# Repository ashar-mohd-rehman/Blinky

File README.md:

Blinky Board is 555 blinky pcb where 10leds blink. The speed can be adjusted via on board potentiometer. Since ne555
timer doesnt have enough pins we use cd4017 gpio extender for using 10 leds

# Schematic #

# Pcb #

# 3d model # 

# Render #

link to BOM : https://docs.google.com/spreadsheets/d/1oSV3quS0oqQWDv8-AmcpKySihurtdW80pACxGFzfaJI/edit?usp=sharing

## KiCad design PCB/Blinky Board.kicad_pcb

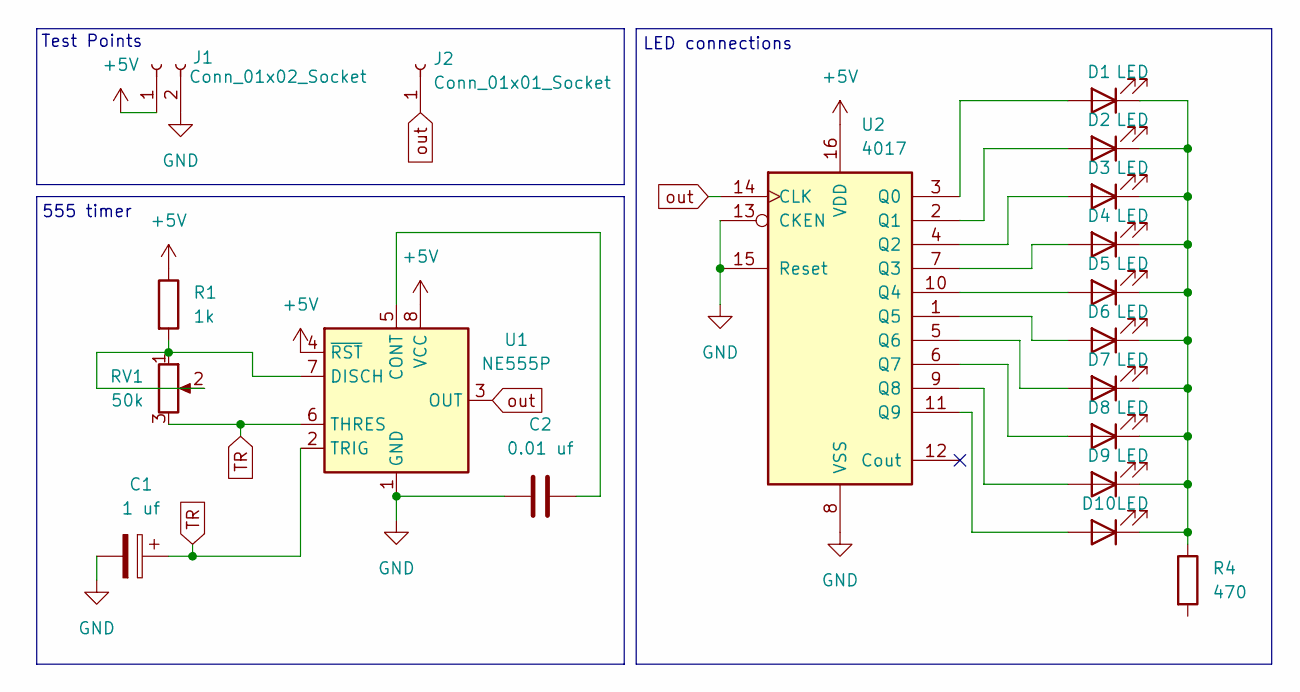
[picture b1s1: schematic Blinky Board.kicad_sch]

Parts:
C1: 1 uf; CP_Radial_D5.0mm_P2.00mm
C2: 0.01 uf; C_Disc_D7.5mm_W2.5mm_P5.00mm
D1, D2, D3, D4, D5, D6, D7, D8, D9, D10: LED; LED_D3.0mm
J1: Conn_01x02_Socket; PinHeader_1x02_P2.54mm_Vertical
J2: Conn_01x01_Socket; PinHeader_1x01_P2.54mm_Vertical
R1: 1k; R_Axial_DIN0207_L6.3mm_D2.5mm_P7.62mm_Horizontal
R4: 470; R_Axial_DIN0207_L6.3mm_D2.5mm_P7.62mm_Horizontal
RV1: 50k; Potentiometer_Vishay_T93YA_Vertical
U1: NE555P; DIP-8_W7.62mm
U2: 4017; CD4017

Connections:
+5V: J1.1, R1.1, U1.4 (~RST), U1.8 (VCC), U2.16 (VDD)
GND: C1.2, C2.1, J1.2, U1.1 (GND), U2.8 (VSS), U2.13 (CKEN), U2.15 (Reset)
unnamed: D1.2 (A), U2.3 (Q0)
unnamed: D1.1 (K), D2.1 (K), D3.1 (K), D4.1 (K), D5.1 (K), D6.1 (K), D7.1 (K), D8.1 (K), D9.1 (K), D10.1 (K), R4.1
unnamed: D2.2 (A), U2.2 (Q1)
unnamed: D3.2 (A), U2.4 (Q2)
unnamed: D4.2 (A), U2.7 (Q3)
unnamed: D5.2 (A), U2.10 (Q4)
unnamed: D6.2 (A), U2.1 (Q5)
unnamed: D7.2 (A), U2.5 (Q6)
unnamed: D8.2 (A), U2.6 (Q7)
unnamed: D9.2 (A), U2.9 (Q8)
unnamed: D10.2 (A), U2.11 (Q9)
unnamed: C2.2, U1.5 (CONT)
unnamed: R1.2, RV1.1, RV1.2, U1.7 (DISCH)
TR: C1.1, RV1.3, U1.2 (TRIG), U1.6 (THRES)
out: J2.1, U1.3 (OUT), U2.14 (CLK)

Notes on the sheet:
555 timer
Test Points
LED connections

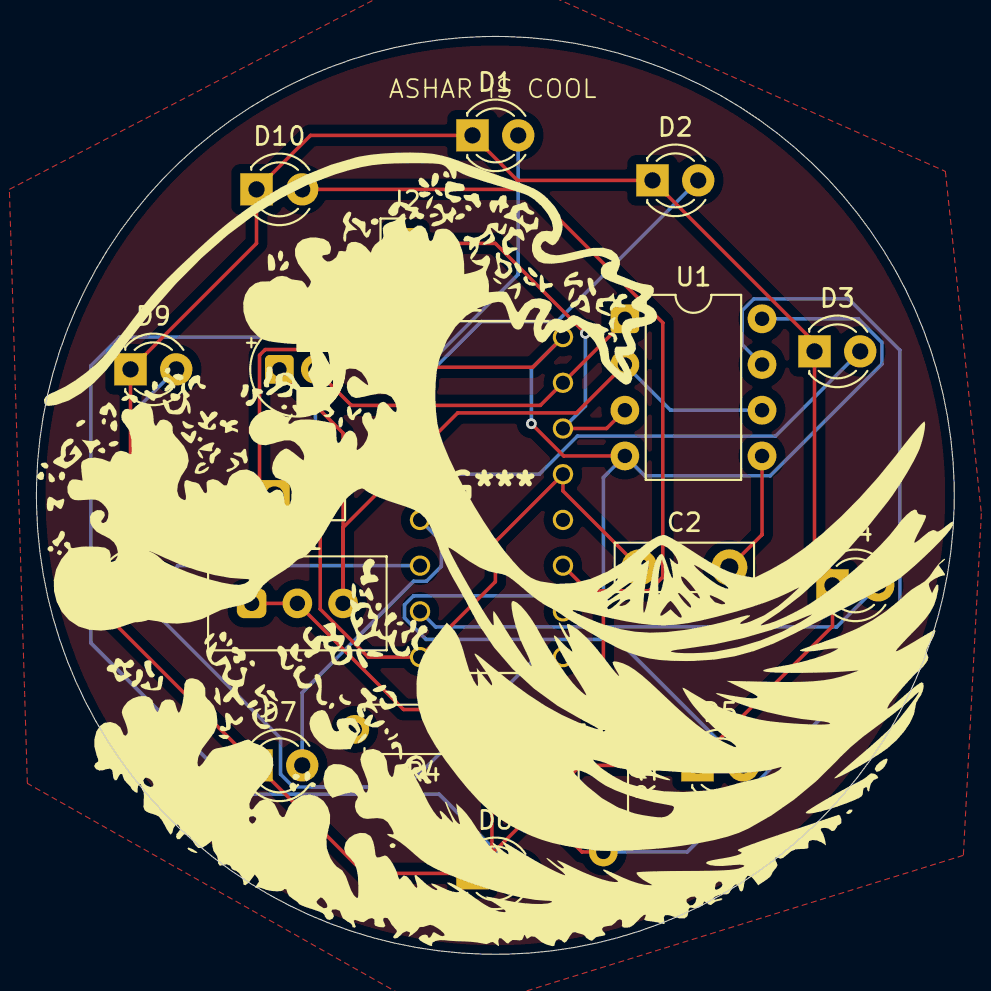
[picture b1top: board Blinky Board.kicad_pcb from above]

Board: 2 copper layers, 51.0 x 51.0 mm, 19 parts (0 on the bottom side), 17 nets.
